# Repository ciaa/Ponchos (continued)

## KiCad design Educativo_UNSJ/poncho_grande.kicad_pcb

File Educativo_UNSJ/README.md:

# Poncho Educativo de la UNSJ #
* Autor: Sarmiento, Leandro Gustavo
* Facultad de Ingeniería – Universidad Nacional de San Juan (FI-UNSJ)

El poncho consta de elemento digitales y analógicos tales
como: potenciómetro, buzzer, UART/RS-232, LCD 16x2, teclado matricial 4x3, y pinout para
comunicaciones varias y pines de propósito general.

Ver información sobre el Poncho en el siguiente PDF:
* [Reporte Poncho Educativo UNSJ.PDF](https://github.com/ciaa/Ponchos/raw/master/Educativo_UNSJ/doc/Informe%20Poncho%20Final%20CIAA02.pdf)
* [Wiki Proyeto CIAA](http://www.proyecto-ciaa.com.ar/devwiki/doku.php?id=repo:ponchos:educativounsj)

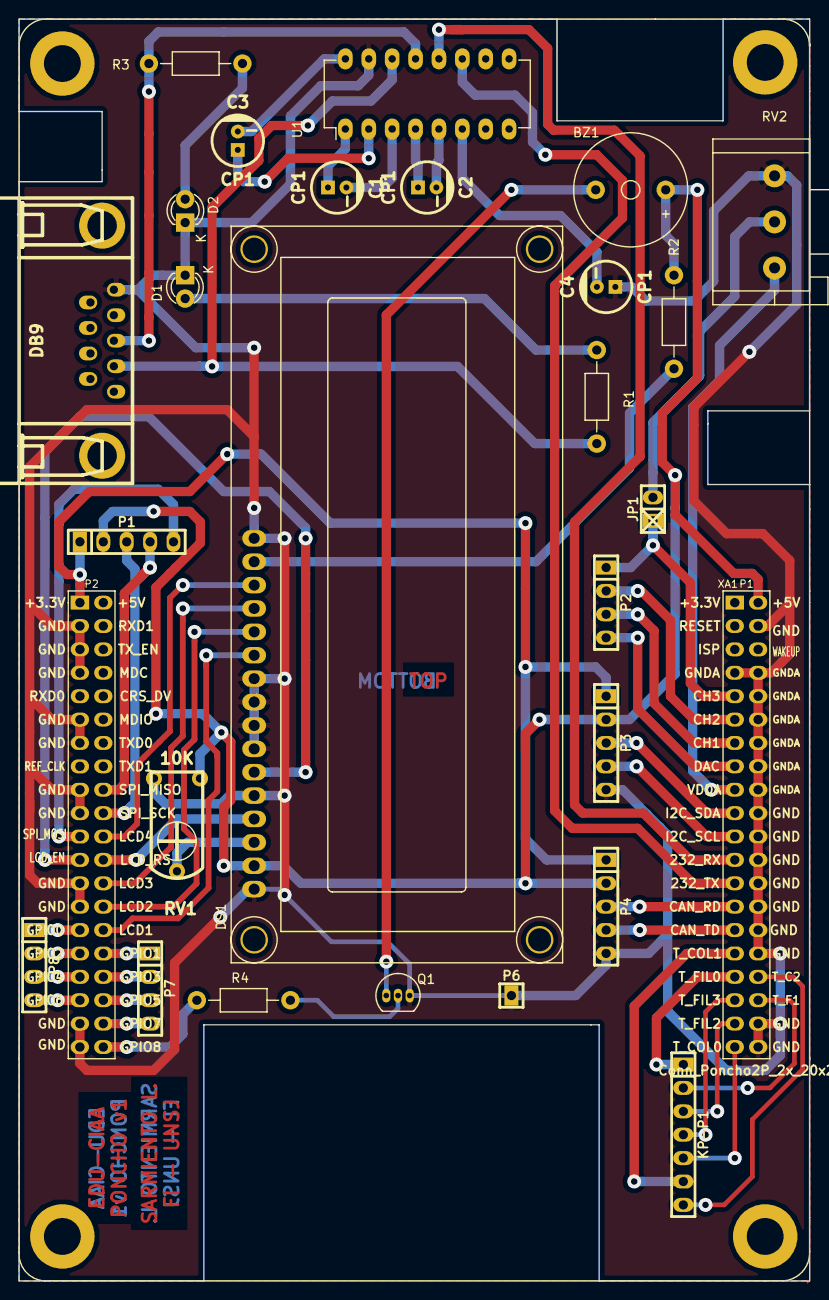
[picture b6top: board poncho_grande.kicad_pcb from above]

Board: 2 copper layers, 85.9 x 137.0 mm, 27 parts (0 on the bottom side), 55 nets.

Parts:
BZ1: buzzer; Buzzer_12x9.5RM7.6
C1, C2, C3, C4: CP1; CP_5x11mm
D1, D2: Led_Small; LED-3MM
DS1: LCD16X2; WC1602A
J1: DB9; DB_9F
JP1: JUMPER; pin_strip_2
KP-P1: Keypad_-_Phone; pin_socket_7
P1, P3, P4: CONN_01X05; pin_strip_5
P2, P7, P8: CONN_01X04; pin_strip_4
P6: CONN_01X01; pin_strip_1
Q1: BC548; TO-92_Inline_Narrow_Oval
R1, R3: 470; Resistor_Horizontal_RM10mm
R2: 100; Resistor_Horizontal_RM10mm
R4: 1K; Resistor_Horizontal_RM10mm
RV1: 10K; trimmer_piher_pt10xv
RV2: 10K; Potentiometer_Alps-RK16-single
U1: MAX232; DIP-16_W7.62mm_LongPads
XA1: Conn_Poncho2P_2x_20x2; poncho_grande

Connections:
+3.3VADC: RV2.3, XA1.17
+3.3VP: P1.1, P3.1, P4.1, XA1.41
+5V: BZ1.1, DS1.2, P1.2, P3.2, P4.2, R2.1, RV1.1, XA1.2
/Circuito Principal/ADC1: P2.3, XA1.13
/Circuito Principal/ADC2: P2.2, XA1.11
/Circuito Principal/ADC3: JP1.1, P2.1, XA1.9
/Circuito Principal/COL0: KP-P1.5, XA1.39
/Circuito Principal/COL1: KP-P1.6, XA1.31
/Circuito Principal/COL2: KP-P1.7, XA1.34
/Circuito Principal/DAC: P2.4, XA1.15
/Circuito Principal/F0: KP-P1.1, XA1.33
/Circuito Principal/F1: KP-P1.2, XA1.36
/Circuito Principal/F2: KP-P1.3, XA1.37
/Circuito Principal/F3: KP-P1.4, XA1.35
/Circuito Principal/GPIO0: P8.1, XA1.69
/Circuito Principal/GPIO1: P7.1, XA1.72
/Circuito Principal/GPIO2: P8.2, XA1.71
/Circuito Principal/GPIO3: P7.2, XA1.74
/Circuito Principal/GPIO4: P8.3, XA1.73
/Circuito Principal/GPIO5: P7.3, XA1.76
/Circuito Principal/GPIO6: P8.4, XA1.75
/Circuito Principal/GPIO7: P7.4, XA1.78
/Circuito Principal/GPIO8: R4.2, XA1.80
/Circuito Principal/LCD1: DS1.11, XA1.70
/Circuito Principal/LCD2: DS1.12, XA1.68
/Circuito Principal/LCD3: DS1.13, XA1.66
/Circuito Principal/LCD4: DS1.14, XA1.62
/Circuito Principal/LCD_EN: DS1.6, XA1.63
/Circuito Principal/MISO: P1.4, XA1.58
/Circuito Principal/MOSI: P1.5, XA1.61
/Circuito Principal/RD: P4.3, XA1.27
/Circuito Principal/RS: DS1.4, XA1.64
/Circuito Principal/RXD: U1.12, XA1.23
/Circuito Principal/SCL: P3.4, XA1.21
/Circuito Principal/SDA: P3.3, XA1.19
/Circuito Principal/TD: P4.4, XA1.29
/Circuito Principal/TXD: U1.11, XA1.25
/Circuito Principal/spiCCK: P1.3, XA1.60
GND: C4.1, D1.1, D2.1, DS1.1, DS1.5, DS1.7, DS1.8, DS1.9, DS1.10, DS1.16, J1.5, P3.5, P4.5, P6.1, Q1.3, RV1.3, RV2.1, U1.15, XA1.4, XA1.7, XA1.8, XA1.10, XA1.12, XA1.14, XA1.16, XA1.18, XA1.20, XA1.22, XA1.24, XA1.26, XA1.28, XA1.30, XA1.32, XA1.38, XA1.40, XA1.43, XA1.45, XA1.47, XA1.51, XA1.53, XA1.57, XA1.59, XA1.65, XA1.67, XA1.77, XA1.79
unnamed: BZ1.2, Q1.1
unnamed: C1.1, U1.1
unnamed: C1.2, U1.3
unnamed: C2.1, U1.4
unnamed: C2.2, U1.5
unnamed: C3.1, U1.2
unnamed: C3.2, U1.16
unnamed: C4.2, U1.6
unnamed: D1.2, R1.1
unnamed: D2.2, R3.1
unnamed: DS1.3, RV1.2
unnamed: DS1.15, R2.2
unnamed: J1.2, R1.2, U1.14
unnamed: J1.3, R3.2, U1.13
unnamed: JP1.2, RV2.2
unnamed: Q1.2, R4.1

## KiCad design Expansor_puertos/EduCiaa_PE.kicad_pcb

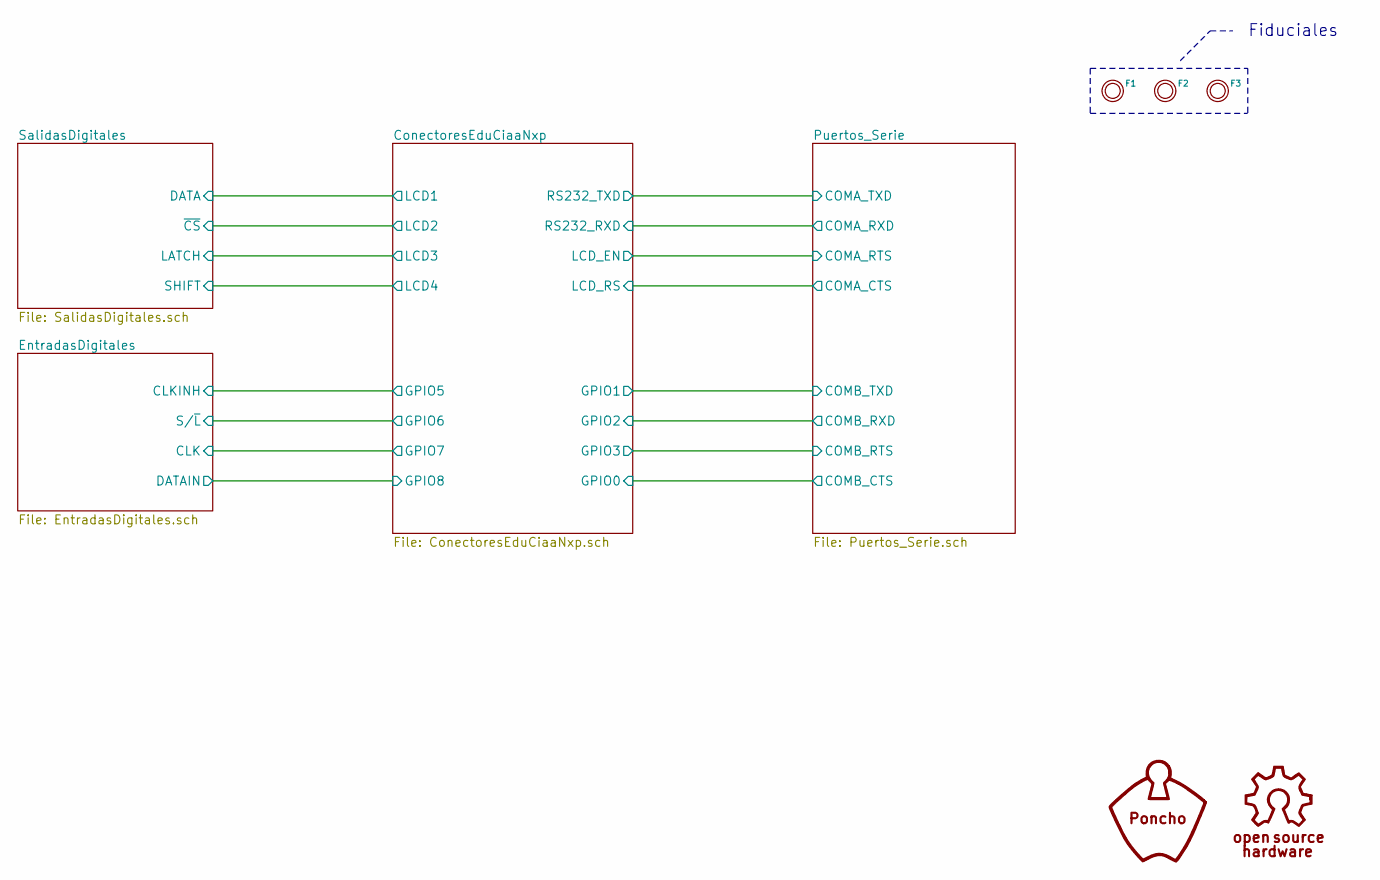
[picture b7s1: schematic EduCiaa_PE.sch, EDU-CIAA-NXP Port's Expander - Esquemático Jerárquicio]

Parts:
F1, F2, F3: FIDUCIAL; Fiducial_1mm

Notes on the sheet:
Fiduciales

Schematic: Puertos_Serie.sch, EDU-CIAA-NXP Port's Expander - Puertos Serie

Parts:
C1, C2, C3, C4, C5, C6, C7, C8: 100nF; C_0805_HandSoldering; Digikey# 311-1142-1-ND
J1, J2: DB9; DB9_F_TH; Digikey# A35107-ND
U1, U2: MAX3232; SOIC-16N; Digikey# 296-13095-1-ND

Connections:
/Puertos_Serie/COMA_CTS: U1.9; also elsewhere on the board
/Puertos_Serie/COMA_RTS: U1.10; also elsewhere on the board
/Puertos_Serie/COMA_RXD: U1.12; also elsewhere on the board
/Puertos_Serie/COMA_TXD: U1.11; also elsewhere on the board
/Puertos_Serie/COMB_CTS: U2.9; also elsewhere on the board
/Puertos_Serie/COMB_RTS: U2.10; also elsewhere on the board
/Puertos_Serie/COMB_RXD: U2.12; also elsewhere on the board
/Puertos_Serie/COMB_TXD: U2.11; also elsewhere on the board
GND: C5.1, C6.1, C7.1, C8.1, J1.5, J2.5, U1.15, U2.15; also elsewhere on the board
unnamed: C1.1, U1.1
unnamed: C1.2, U1.3
unnamed: C2.1, U2.1
unnamed: C2.2, U2.3
unnamed: C3.1, U1.4
unnamed: C3.2, U1.5
unnamed: C4.1, U2.4
unnamed: C4.2, U2.5
unnamed: C5.2, U1.2
unnamed: C6.2, U1.6
unnamed: C7.2, U2.2
unnamed: C8.2, U2.6
unnamed: J1.2, U1.14
unnamed: J1.3, U1.13
unnamed: J1.7, U1.8
unnamed: J1.8, U1.7
unnamed: J2.2, U2.14
unnamed: J2.3, U2.13
unnamed: J2.7, U2.8
unnamed: J2.8, U2.7

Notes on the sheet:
Puertos Serie RS-232
COM1
COM2

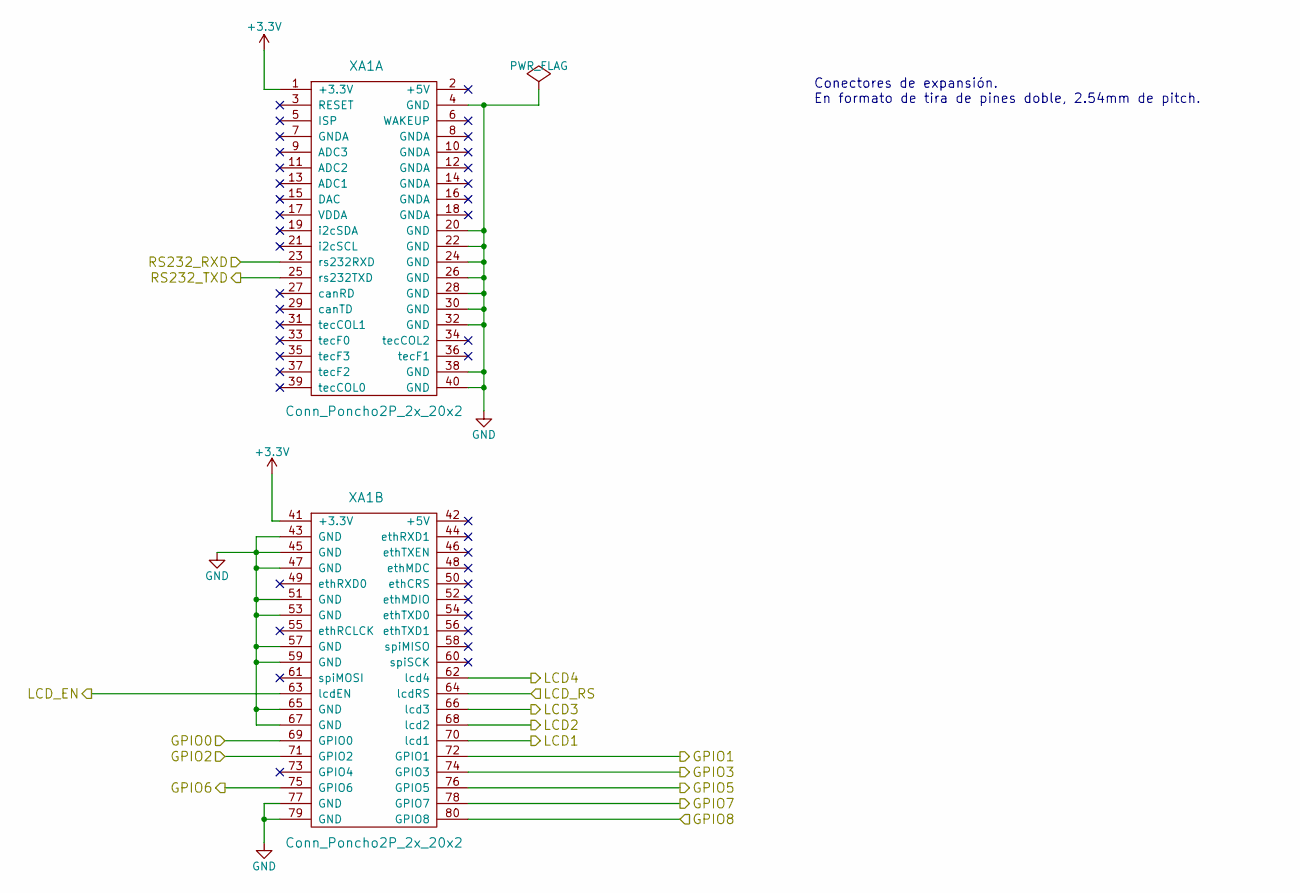
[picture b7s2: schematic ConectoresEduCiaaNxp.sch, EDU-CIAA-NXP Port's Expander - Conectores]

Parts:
XA1: Conn_Poncho2P_2x_20x2; Conn_Poncho_Completo

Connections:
/ConectoresEduCiaaNxp/GPIO6: XA1.75 (GPIO6); also elsewhere on the board
/ConectoresEduCiaaNxp/LCD2: XA1.68 (lcd2); also elsewhere on the board
/ConectoresEduCiaaNxp/LCD4: XA1.62 (lcd4); also elsewhere on the board
/EntradasDigitales/CLK: XA1.78 (GPIO7); also elsewhere on the board
/EntradasDigitales/CLKINH: XA1.76 (GPIO5); also elsewhere on the board
/EntradasDigitales/DATAIN: XA1.80 (GPIO8); also elsewhere on the board
/Puertos_Serie/COMA_CTS: XA1.64 (lcdRS); also elsewhere on the board
/Puertos_Serie/COMA_RTS: XA1.63 (lcdEN); also elsewhere on the board
/Puertos_Serie/COMA_RXD: XA1.23 (rs232RXD); also elsewhere on the board
/Puertos_Serie/COMA_TXD: XA1.25 (rs232TXD); also elsewhere on the board
/Puertos_Serie/COMB_CTS: XA1.69 (GPIO0); also elsewhere on the board
/Puertos_Serie/COMB_RTS: XA1.74 (GPIO3); also elsewhere on the board
/Puertos_Serie/COMB_RXD: XA1.71 (GPIO2); also elsewhere on the board
/Puertos_Serie/COMB_TXD: XA1.72 (GPIO1); also elsewhere on the board
/SalidasDigitales/DATA: XA1.70 (lcd1); also elsewhere on the board
/SalidasDigitales/LATCH: XA1.66 (lcd3); also elsewhere on the board
GND: XA1.4 (GND), XA1.20 (GND), XA1.22 (GND), XA1.24 (GND), XA1.26 (GND), XA1.28 (GND), XA1.30 (GND), XA1.32 (GND), XA1.38 (GND), XA1.40 (GND), XA1.43 (GND), XA1.45 (GND), XA1.47 (GND), XA1.51 (GND), XA1.53 (GND), XA1.57 (GND), XA1.59 (GND), XA1.65 (GND), XA1.67 (GND), XA1.77 (GND), XA1.79 (GND); also elsewhere on the board

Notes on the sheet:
Conectores de expansión. En formato de tira de pines doble, 2.54mm de pitch.

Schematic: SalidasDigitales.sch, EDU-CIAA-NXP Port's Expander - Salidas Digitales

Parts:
C9, C10: 100nF; C_0805_HandSoldering; Digikey# 311-1142-1-ND
J3, J4, J9: TB_1X2; bornier2; Digikey# ED2609-ND
J5, J6, J7, J8: TB_1X3; bornier3; Digikey# ED2610-ND
R1: 10K; R_0805_HandSoldering; Digikey# 311-10KARCT-ND
U3, U4: 74HC595; SOIC-16N; Digikey# MM74HC595MXCT-ND
U5, U6: ULN2803A; SOIC-18; Digikey# 296-15777-1-ND

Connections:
/ConectoresEduCiaaNxp/LCD2: R1.1, U3.13, U4.13; also elsewhere on the board
/ConectoresEduCiaaNxp/LCD4: U3.11, U4.11; also elsewhere on the board
/SalidasDigitales/COMUN: J9.1, U5.10, U6.10
/SalidasDigitales/DATA: U3.14; also elsewhere on the board
/SalidasDigitales/LATCH: U3.12, U4.12; also elsewhere on the board
/SalidasDigitales/OUT0: J3.2, U5.18
/SalidasDigitales/OUT1: J3.1, U5.17
/SalidasDigitales/OUT2: J4.2, U5.16
/SalidasDigitales/OUT3: J4.1, U5.15
/SalidasDigitales/OUT4: J5.3, U5.14
/SalidasDigitales/OUT5: J5.2, U5.13
/SalidasDigitales/OUT6: J5.1, U5.12
/SalidasDigitales/OUT7: J6.3, U5.11
/SalidasDigitales/OUT8: J6.2, U6.18
/SalidasDigitales/OUT9: J6.1, U6.17
/SalidasDigitales/OUT10: J7.3, U6.16
/SalidasDigitales/OUT11: J7.2, U6.15
/SalidasDigitales/OUT12: J7.1, U6.14
/SalidasDigitales/OUT13: J8.3, U6.13
/SalidasDigitales/OUT14: J8.2, U6.12
/SalidasDigitales/OUT15: J8.1, U6.11
GND: C9.2, C10.1, J9.2, U3.8, U4.8, U5.9, U6.9; also elsewhere on the board
unnamed: U3.1, U5.2
unnamed: U3.2, U5.3
unnamed: U3.3, U5.4
unnamed: U3.4, U5.5
unnamed: U3.5, U5.6
unnamed: U3.6, U5.7
unnamed: U3.7, U5.8
unnamed: U3.9, U4.14
unnamed: U3.15, U5.1
unnamed: U4.1, U6.2
unnamed: U4.2, U6.3
unnamed: U4.3, U6.4
unnamed: U4.4, U6.5
unnamed: U4.5, U6.6
unnamed: U4.6, U6.7
unnamed: U4.7, U6.8
unnamed: U4.15, U6.1

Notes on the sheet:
Fuente hasta 45V
CARGA

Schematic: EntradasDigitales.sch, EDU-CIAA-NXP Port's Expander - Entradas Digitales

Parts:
C11, C12: 100nF; C_0805_HandSoldering; Digikey# 311-1142-1-ND
J10, J11, J16: TB_1X2; bornier2; Digikey# ED2609-ND
J12, J13, J14, J15: TB_1X3; bornier3; Digikey# ED2610-ND
R2, R3, R4, R5, R6, R7, R8, R9, R10, R11, R12, R13, R14, R15, R16, R17: 10K; R_0805_HandSoldering; Digikey# 311-10KARCT-ND
U7, U8: ULN2803A; SOIC-18; Digikey# 296-15777-1-ND
U9, U10: 74HC165; SOIC-16N; Digikey# 296-8249-5-ND

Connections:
/ConectoresEduCiaaNxp/GPIO6: U9.1, U10.1; also elsewhere on the board
/EntradasDigitales/CLK: U9.2, U10.2; also elsewhere on the board
/EntradasDigitales/CLKINH: U9.15, U10.15; also elsewhere on the board
/EntradasDigitales/DATAIN: U10.9; also elsewhere on the board
/EntradasDigitales/I0: R2.2, U7.18, U9.11
/EntradasDigitales/I1: R4.2, U7.17, U9.12
/EntradasDigitales/I2: R6.2, U7.16, U9.13
/EntradasDigitales/I3: R8.2, U7.15, U9.14
/EntradasDigitales/I4: R10.2, U7.14, U9.3
/EntradasDigitales/I5: R12.2, U7.13, U9.4
/EntradasDigitales/I6: R14.2, U7.12, U9.5
/EntradasDigitales/I7: R16.2, U7.11, U9.6
/EntradasDigitales/I8: R3.2, U8.18, U10.11
/EntradasDigitales/I9: R5.2, U8.17, U10.12
/EntradasDigitales/I10: R7.2, U8.16, U10.13
/EntradasDigitales/I11: R9.2, U8.15, U10.14
/EntradasDigitales/I12: R11.2, U8.14, U10.3
/EntradasDigitales/I13: R13.2, U8.13, U10.4
/EntradasDigitales/I14: R15.2, U8.12, U10.5
/EntradasDigitales/I15: R17.2, U8.11, U10.6
/EntradasDigitales/IN00: J10.1, U7.1
/EntradasDigitales/IN01: J10.2, U7.2
/EntradasDigitales/IN02: J11.1, U7.3
/EntradasDigitales/IN03: J11.2, U7.4
/EntradasDigitales/IN04: J12.1, U7.5
/EntradasDigitales/IN05: J12.2, U7.6
/EntradasDigitales/IN06: J12.3, U7.7
/EntradasDigitales/IN07: J13.1, U7.8
/EntradasDigitales/IN08: J13.2, U8.1
/EntradasDigitales/IN09: J13.3, U8.2
/EntradasDigitales/IN10: J14.1, U8.3
/EntradasDigitales/IN11: J14.2, U8.4
/EntradasDigitales/IN12: J14.3, U8.5
/EntradasDigitales/IN13: J15.1, U8.6
/EntradasDigitales/IN14: J15.2, U8.7
/EntradasDigitales/IN15: J15.3, U8.8
GND: C11.2, C12.2, J16.1, J16.2, U7.9, U8.9, U9.8, U9.10, U10.8; also elsewhere on the board
unnamed: U9.9, U10.10

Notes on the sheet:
Fuente hasta 28V

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
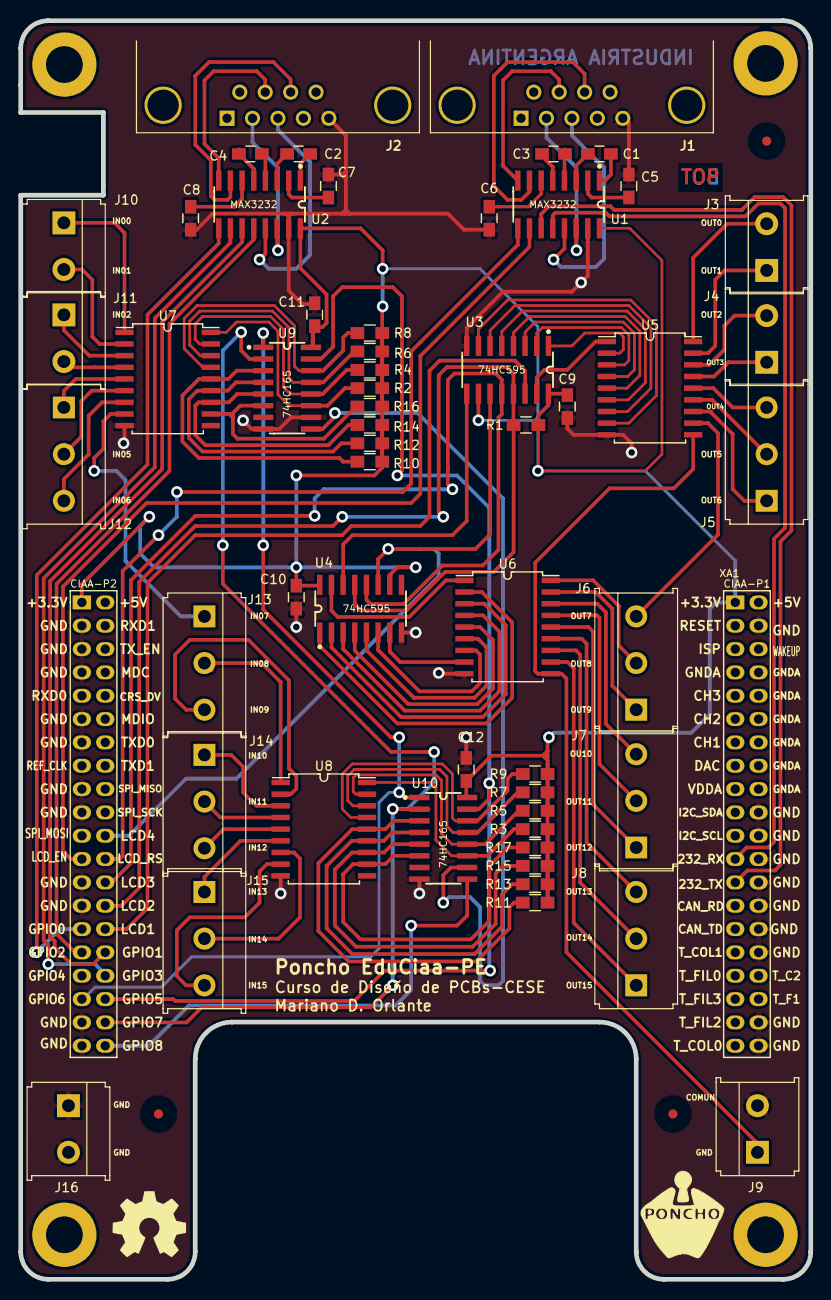
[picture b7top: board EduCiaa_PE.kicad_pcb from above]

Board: 2 copper layers, 86.0 x 137.0 mm, 61 parts (0 on the bottom side), 105 nets.

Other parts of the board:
G1: LOGO; Logo_Poncho
G2: Logo_OSHWA

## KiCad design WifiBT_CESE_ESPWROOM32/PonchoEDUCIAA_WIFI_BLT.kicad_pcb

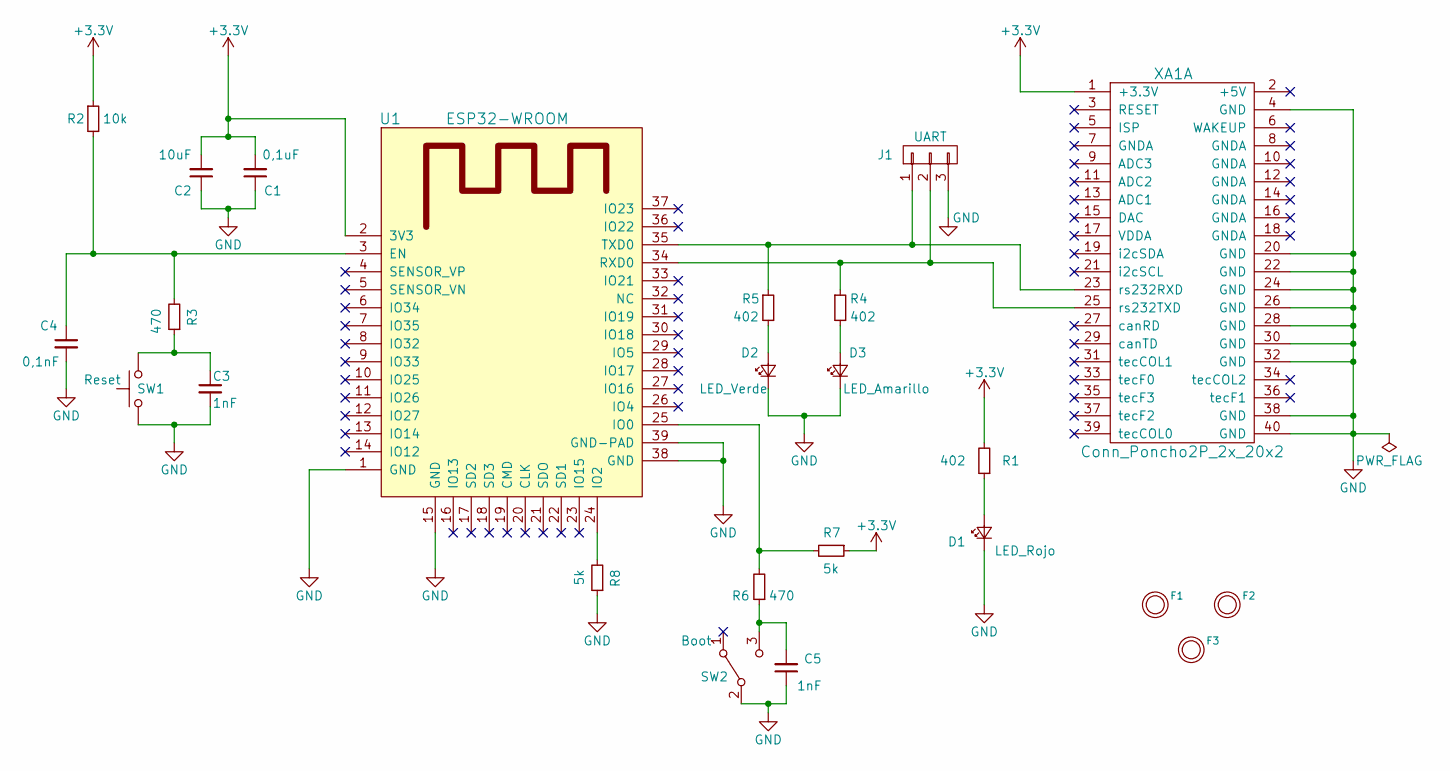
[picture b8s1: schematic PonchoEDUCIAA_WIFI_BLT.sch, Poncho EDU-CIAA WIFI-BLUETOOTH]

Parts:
C1: 0,1uF; C_0603_HandSoldering; Mouser# 581-02016D104KAT2A; Digikey# 478-5266-1-ND
C2: 10uF; C_0603_HandSoldering; Mouser# 81-GRM219R60J106KE9D; Digikey# 490-3340-1-ND
C3: 1nF; C_0603_HandSoldering; Mouser# 81-GRM1555C1H101JA1D; Digikey# 490-5922-1-ND
C4: 0,1nF; C_0603_HandSoldering; Mouser# 81-GRM1555C1H100JA1D; Digikey# 490-5921-1-ND
C5: 1nF; C_0603_HandSoldering; Mouser# 581-0201ZA101JAT2A; Digikey# 478-1026-1-ND
D1: LED_Rojo; LED_0805; Mouser# 720-LSR976-NR-1; Digikey# 475-1278-1-ND
D2: LED_Verde; LED_0805; Mouser# 720-LGR971-KN-1; Digikey# 475-1410-1-ND
D3: LED_Amarillo; LED_0805; Mouser# 720-LYR976-PS-36; Digikey# 475-2560-1-ND
F1, F2, F3: FIDUCIAL; Fiducial_1mm
J1: UART; CON_PALETA_3; Mouser# 538-22-27-2031; Digikey# WM4112-ND
R1, R4, R5: 402; R_0805_HandSoldering; Mouser# 603-RC0805FR-07402RL; Digikey# 311-402CRCT-ND
R2: 10k; R_0805_HandSoldering; Mouser# 667-ERA-6AEB103V; Digikey# P10KDACT-ND
R3, R6: 470; R_0805_HandSoldering; Mouser# 603-RC0805FR-07470RL; Digikey# 311-470CRCT-ND
R7, R8: 5k; R_0805_HandSoldering; Mouser# 71-CRCW0805-5K; Digikey# CRCW08055K00FKTA-ND
SW1: Reset; SW_PUSH_6mm; Mouser# 611-D6C90F1LFS; Digikey# 401-1969-ND
SW2: Boot; SW_Micro_SPST; Mouser# 611-JS202011CQN; Digikey# 401-2001-ND
U1: ESP32-WROOM; Mouser# 485-3320; Digikey# 1528-1801-ND
XA1: Conn_Poncho2P_2x_20x2; Conn_Poncho_Derecha; Mouser# 855-M50-3501042; Digikey# 952-1386-ND

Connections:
+3V3: C1.2, C2.2, R1.2, R2.1, R7.1, U1.2 (3V3), XA1.1 (+3.3V)
GND: C1.1, C2.1, C3.2, C4.2, C5.1, D1.1 (K), D2.1 (K), D3.1 (K), J1.3, R8.1, SW1.1, SW2.2 (B), U1.1 (GND), U1.15 (GND), U1.38 (GND), U1.39 (GND-PAD), XA1.4 (GND), XA1.20 (GND), XA1.22 (GND), XA1.24 (GND), XA1.26 (GND), XA1.28 (GND), XA1.30 (GND), XA1.32 (GND), XA1.38 (GND), XA1.40 (GND)
unnamed: C3.1, R3.1, SW1.2
unnamed: C4.1, R2.2, R3.2, U1.3 (EN)
unnamed: C5.2, R6.1, SW2.3 (C)
unnamed: D1.2 (A), R1.1
unnamed: D2.2 (A), R5.2
unnamed: D3.2 (A), R4.2
unnamed: J1.1, R5.1, U1.35 (TXD0), XA1.23 (rs232RXD)
unnamed: J1.2, R4.1, U1.34 (RXD0), XA1.25 (rs232TXD)
unnamed: R6.2, R7.2, U1.25 (IO0)
unnamed: R8.2, U1.24 (IO2)

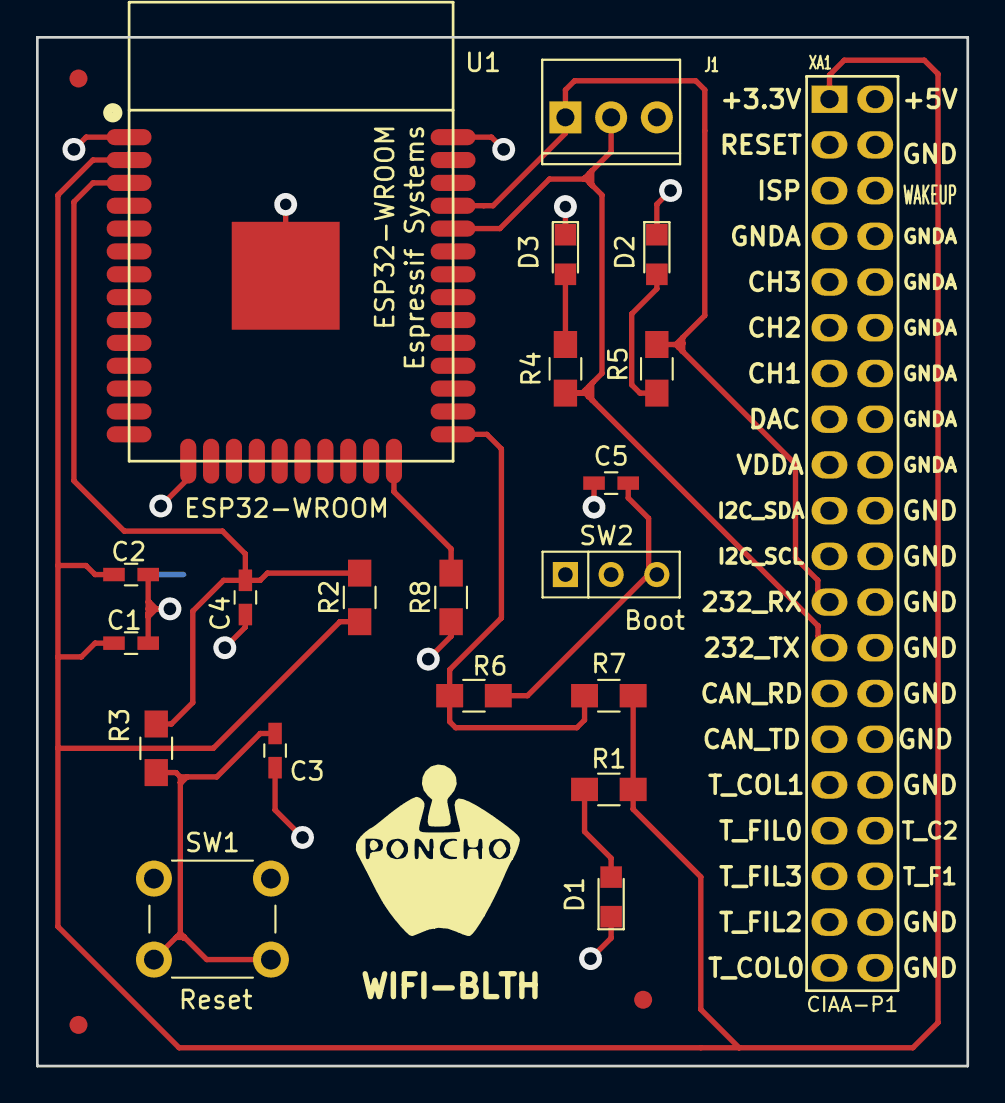
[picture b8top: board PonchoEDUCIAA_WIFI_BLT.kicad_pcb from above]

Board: 2 copper layers, 51.7 x 57.2 mm, 25 parts (0 on the bottom side), 12 nets.

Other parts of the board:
G1: WIFI-BLTH; Logo_Poncho

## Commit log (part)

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2015-10-03 * Agrego LEEME.txt a la documentación de los modelos.
2015-10-05 * Agrego textos instructivos en esquema y PCB.
2015-10-05 * Agrego posición detallada de los leds en la plantilla EDU-CIAA.
2015-10-06 * Agrego agujero para ver led.
2015-10-06 * Agrego nombre del poncho a los iconos de template.
2015-10-06 * Agrego modelo para poncho izquierdo.
2015-10-06 * Agrego ruteo al poncho mediano. Muevo ícono de Template.
2015-10-07 * Cambios menores por conector conn_5 diferente. Limpio bibliotecas .lib.
2015-10-07 * Agrego captura de render del poncho mediano.
2015-10-07 * Agrego capturas del uso de Templates de Kicad.
2015-10-26 Se agregan hojas de datos
2015-12-03 Numeración, corrección de nombres de etiquetas de jerarquía (letra o por cero), pasa el ERC.
2015-12-05 Agrego 1206 para capacitor, corrijo asignación capas de 10uF.
2016-05-12 Agrego LEEME.txt para mencionar el estado del Poncho Ethernet.
2016-05-14 Calculo de posible configuración de par diferencial para impedancia esperada.
2016-05-23 añado expansores para conectores de la CIAA
2016-06-02 agrgo licencia
2016-06-08 Actualización de Netlist con nombres diferenciales.
2016-06-09 Nueva prueba para minimizar ecualización de distancia
2016-06-15 Modificaciones de etiquetas a wires en el esquemático.
2016-06-15 Situado de componentes para trazado de par diferencial.
2016-06-16 Borro archivos innecesarios de Poncho PLC.
2016-06-16 conexión de los componentes criticos de los pares.
2016-06-22 Preliminar de longitudes bien determinadas.
    Conflicts:
    ethernet_LAN8720A_v2/ethernet_LAN8720A_v2.kicad_pcb
2016-07-05 commit inicial
2016-07-07 Modifico el Poncho ETH para que sea solo Poncho Izquierdo.
2016-07-07 Redibujo planos, agrego keepout en diferenciales, quito rulo grande en diferencial, muevo oscilador 50MHZ entre PHY y MAC, muevo capacitores filtro 3.3v.
2016-07-13 Commit Inicial
    Se agrega la Hoja de presentación de proyecto.
2016-07-13 Primera version de los esquematicos a partir del modelo de poncho grande
2016-07-16 Acomdado de serigrafía y algunas pistas para que el pleno llegue a toda la placa.
2016-07-19 cambio de pc
2016-07-19 agregado buzzer y medidor de batería
2016-07-20 Add .gitignore
2016-07-20 Modificacion de la descripcion de hardware.
2016-07-21 Reorganizo bibliotecas en esquemático y PCB. Reparo señal de 12V. Agrego Footprints. Coloco plantilla EDU-CIAA. Reparo asociación conector EDU-CIAA en sch y pcb.
2016-07-21 Correcciones propuestas al Poncho SumoRobot.
2016-07-23 Se realiza el Placement de los componentes y un prerouteo para mostrar que el placement elegido permite un adecuado routeo del mismo.
2016-07-25 Commit message
2016-07-25 Se agregan componentes 3d.
2016-07-26 Cambios de Label.
2016-07-26 Se finaliza el prerouteo y se realizan las primeras correcciones de la revision
    Este routeo cumple chequeo de DRC pero no es definitivo, le faltan planos y detalles finos.
    Se realiza este commit antes de continuar con los demas cambios sugeridos por la revisión que son más peligrosos, como quitar una hoja del esquematico y quitar todos aquellos pines del AX1 que no se 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
2016-07-27 imag3D
2016-07-27 Routeo Definitivo
    Queda pendiente volver locales los footprints y reparar el 3D de la placa
2016-07-27 correcciones menores sobre el PCB
2016-07-27 v1.3
2016-07-30 segundo commit
2016-07-31 se crea footprint de chip ECG
2016-07-31 primeros pasos en PCB
2016-08-01 incorporacion de planos de tierra y alimetacion
2016-08-03 Muevo archivos de Poncho Audio a un subdirectorio.
2016-08-03 Borro Poncho Ethernet viejo (abandonado).
2016-08-04 se generan esquematicosen extencion. pdf
2016-08-05 se agrega Stack - UP
2016-08-07 se agregan mas campos para el BOM y se genran archivos GERBERS
2016-08-10 Agrego Poncho Básico como un modelo adicional.
2016-08-11 Detalles NC y power flag en .sch. Lock conector y anchos pista en PCB.
2016-08-18 se eliminan etiquetas nenecesarias en esquematico y se corrige error
2016-08-19 se vuelve a rutear componentes para no recortar tanto los planos de tierra
2016-08-20 se genera archivo jpg con vista 3D
2016-08-23 se completa el diseño en vista 3D
2016-08-24 Borro archivo de chache.
2016-08-24 Borro archivos ocultos.
2016-09-17 Oculto campos de módulo en el esquemático. Detalles de los rótulos.
2016-09-18 Agrando vías para fabricación nacional 1mm/0,5mm. Mejoro chasis vs. GND. Detalles de ruteo.
2016-09-29 Agrego JP1. Agrego pullup a línea de reset.
2016-09-30 Agrego fiduciales y agujeros al PCB. Configuro DRC. Agrando vía debajo del IC, quito errores de DRC, reorganizo textos.
2016-09-30 Agrego parcialemente la vista 3D en el .kicad_pcb.
2016-10-01 Agrego modelo 3D del oscilador. REVISAR FOOTPRINT DEL MISMO.
2016-10-01 Corrijo el footprint del oscilador. Reorganizo esa zona. Agrego serigrafía. Jumper smd sin tierra entre pads. Mejoro vista 3D.
2016-10-01 Agrego versión a la serigrafía (v0.1).
2016-10-17 Poncho Osciloscopio. Agrego archivos para fabricación.
2016-10-17 Poncho Eth: Agrego archivos de fabricación.
2016-10-30 Avance posicionamiento & Dimensión del poncho
    Se avanzo en el posicionamiento de las entradas.
    Se esta evaluando la dimensión del poncho y la posición de los agujeros
    de sujeción.
    A partir de ahora el diseño esta a cargo del Alumno Ignacio Vetrano
    (E.E.S.T. N°5 - 5to 5ta)
2016-11-05 hojas de datos y esquematico modelo
2016-11-05 se modificó el nombre de los archivos
2016-11-10 primeros componentes en el esquematico
2016-11-11 Inicializacion de estructura de proyecto
2016-11-11 Diseño preliminar del esquemático sin conectores PICO-CIAA
2016-11-12 footprints ok, componentes en pcb
2016-11-18 correcciones en esquemarico. ERC OK. Se crearon rotulos. PCB: replacing mas compacto
2016-11-18 Añadida la primera versión de la plantilla para pico-ciaa
2016-11-19 tamaño placa
    Se ajusto el tamaño de la placa a 100x150mm.
    Avance en posicionamiento.
2016-11-20 ruteo casi terminado. falta modulo wifi
2016-11-21 Primer commit. Listos libs, esquemático y footprints.
2016-11-25 Se agruparon componentes por bloques funcionales. Falta definir contorno de la placa y posicion final de los bloques.
2016-11-26 Placement in progress. XBee module 3d model
2016-11-26 drills ok. fix size de rele
2016-11-26 imagen del modelo 3d
2016-11-28 1.-Esquemático del poncho finalizado. 2.-Añadidas las hojas de dato de referencia para la picoCIAA: Guía de uso, Referencia para el adaptador Arduino (utilizado de referencia solamente para los modos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
2016-12-01 enumero los componentes, asocio los footprint, completo los valores de digikey
2016-12-02 se borraron las bibliotecas
2016-12-03 correcciones pcb 2
2016-12-03 plano de gnd en pcb
2016-12-03 Se agregaron cotas, fiducidales y escrituras en cobre. Tambien se corrigieron algunos errores.
2016-12-12 Reubicacion de optoacopladores, cambio de footoprins de resistencias a 0805, correcion general.Falta arreglar archivos vista 3d y completar los campos #digikey
2016-12-14 Se agrego documentacion del proyecto, se agregaron vistas 3d faltantes y se repararon las extensiones de las que no funcionaban
2016-12-15 Ruteo. Correciones. Cambio de footprint del switch.
2016-12-20 Correcion de pistas a octoacopladores, rutas de modelos 3d, id encoder y otras correcciones menores
2016-12-21 Corrección de BOM del Poncho Osciloscopio.
2016-12-23 Version con correcciones
2016-12-23 Modelos 3d. Correción de ruteo. Textos.
2016-12-24 se elimina carpeta DOC, se agregan serigrafias
2017-01-10 Reorganizo Poncho Educativo1.
2017-01-10 Reorganizo directorios del Poncho Misión SAE.
2017-01-10 Reorganizo directorio del Poncho Oxímetro.
2017-01-11 Agrego imagen de Poncho Ethernet.
2017-01-11 Agrego renders de ponchos en repos externos.
2017-01-11 Expansores CIAA 10x2: Corrijo borde pcb, serigrafía y agrego render para la wiki.
2017-02-01 Agrego otro collage de vistas 3D de Ponchos.
2017-03-04 Avance routeo
    Se routearon las pistas de GNDA que estaban sin conectar.
    Se agregaron vias y areas de cobre en las salidas de los mosfet para
    alivio termico.
2017-04-07 Template Poncho superior para PicoCIAA
    Primer versión de un template para poder diseñar ponchos que coloquen
    por encima de la PicoCIAA.
2017-05-15 Commit Inicial
    > Se crea la estructura de carpetas.
    > Se incluye una lista tentativa de requisitos específicos.
2017-05-19 Se crea proyecto de KiCad
    > Se crea el proyecto de Kicad.
    > Se configuran los paths correspondientes.
    > Se retiran librerías ajenas al proyecto.
    > Se crea la jerarquía tentativa del proyecto.
2017-05-19 Primera iteración sobre esquemático de Interfaz MIDI
    > Primer layout de componentes y correspondiente conexionado de los mismos, en vistas de aplicar mejoras posteriores.
2017-05-21 Se prosigue con el trabajo en el esquemático
    > Segunda iteración sobre el esquemático de la Interfaz MIDI: se reubican algunos componentes para mejorar el aspecto general.
    > Se reemplaza símbolo de encoder en el correspondiente esquemático, colocando la electrónica correspondiente para la adecuación de señal generada.
    > Completado de rótulo en varios esquemáticos.
2017-06-11 Corrección menor de librería de símbolos
    > Se corrige numeración de algunos pads en el símbolo ENCODER_w_SWITCH.
    > Se modifican propiedades de pines de alimentación 3,3v y 5v en el símbolo Conn_Poncho2P_2x_20x2 para evitar falsos errores de ERC.
2017-06-14 Ordenamiento
    > Se elimina hoja de esquemático jerárquico que no se utilizó.
2017-06-14 Corrección menor de librería de símbolos
    Se corrige asignación incorrecta de pines en símbolo multiparte regular de CD40106.
2017-06-18 Se corrige error en el esquematico
    > Se elimina conexión errónea entre 5v y GND en el conector XA1B.
    > Se incluye power flag conectado a GND.
    > Se reasignan las compuertas del buffer CD4050 para facilitar el ruteo.
    > Se trabaja sobre archivo de PCB:
    > Se completa el rótulo.
    > Se reacomodan los footprints según su relación con los componentes principales.
2017-06-26 Agrego informe y fotos que me pasó Leandro Sarmiento, del poncho educativo de la UNSJ.
2017-07-03 Actualización de Readme.md
    Corrección de dos errores ortográficos menores.
2017-07-12 Se trabaja en modelo 3D
    > Se elimina archivo auxiliar.
    > Se modifican las propiedades del modelo.
2017-07-12 Realizados algunos cambios según 1ra Revisión
    > Se realizan correcciones al proyecto según lo expuesto en columna "Acción tomada" de documento de revisión correspondiente.
2017-07-12 Se corrige error en hoja de proyecto
    > Se corrige un error en los requisitos específicos: donde debía leerse "11. Su diseño no debe resultar prohibitivo(...)" se leía "11. Su diseño de debe resultar prohibitivo(...)"
2017-07-12 Se modifica Footprint del teclado
    > Se reduce el área para que no haya superposición del mismo sobre los pines de los conectores (tiras de pines).
2017-07-15 Se corrige posición de modelo 3D
    > Se corrige los parametros de ajuste para el posicionamiento del modelo 3D correspondientes al footprint del header 2x20.
2017-07-17 Correciones menores
    > Se elimina nombre de componentes ( tiras de pines ) de la capa de serigrafía.
    > Se realizan correciones menores al ruteo y se agregan vías para conectar plano de masa en capa bottom y conector derecho en capa front.
2017-07-17 Correcciones menores en campos para BOM
    > Se corrigen error observados luego de la generación de la BOM.
2017-08-05 Se incluye documento de 2da Revisión
    > Se incluye documento de la revisión realizada por Mg. Ing Diego Brengi.
2017-08-19 Se incluyen Gerbers
    > Se incluyen Gerbers, mapa y reporte de perforado.
2017-08-20 Se incluyen dimensiones y archivo Readme
    > Se incluyen:
    > dimensiones del poncho
    > figuras
    > Readme
2017-08-24 Detalles de la vista 3d.
2017-09-15 Agrego render MIDI.
2017-09-16 Agrego Poncho Wifi-BT ESPWROOM32 desde https://github.com/gcocce/poncho_EDU-CIAA_wifi_blth
2017-09-16 Corrijo modelos 3D locales para el poncho educativo UNSJ. Agrego render 3D.
2017-09-26 Actualizo Poncho pico-wifi desde https://github.com/sergiordj/Poncho_wifi_picociaa
2017-10-09 Agrego modificaciones enviadas por ivan.s@cika.com para que el hardware sea compatible con el firmware de comandos AT del módulo.
